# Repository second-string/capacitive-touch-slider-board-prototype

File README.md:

# capacitive-touch-slider-board-prototype

This repo contains a design for a prototype PCB for testing different capacitive touch slider designs. For more information on the different slider footprints, see [writeup](https://brian.team/engineering/capacitive-touch-protoype-pcbs/).

There is a schematic PDF and PCB layer prints PDF in the version 1.0 directory if you do not have KiCad. There are also Excel and interactive BOMs in the `bom/` subdirectory.

Reach out if you would like the KiCad slider schematic symbol and footprint files, they are saved in my global library and so not directly accessible from the project directory.

There is test firmware in `slider-board_rev_1_0/bringup_firmware/`. **NOTE:** This firmware is sloppy, terribly written, inefficient, and everything is hardcoded. It is only included as a reference, do not think that this will work for you out of the box.

Videos of example behavior are in the `img/` directory.

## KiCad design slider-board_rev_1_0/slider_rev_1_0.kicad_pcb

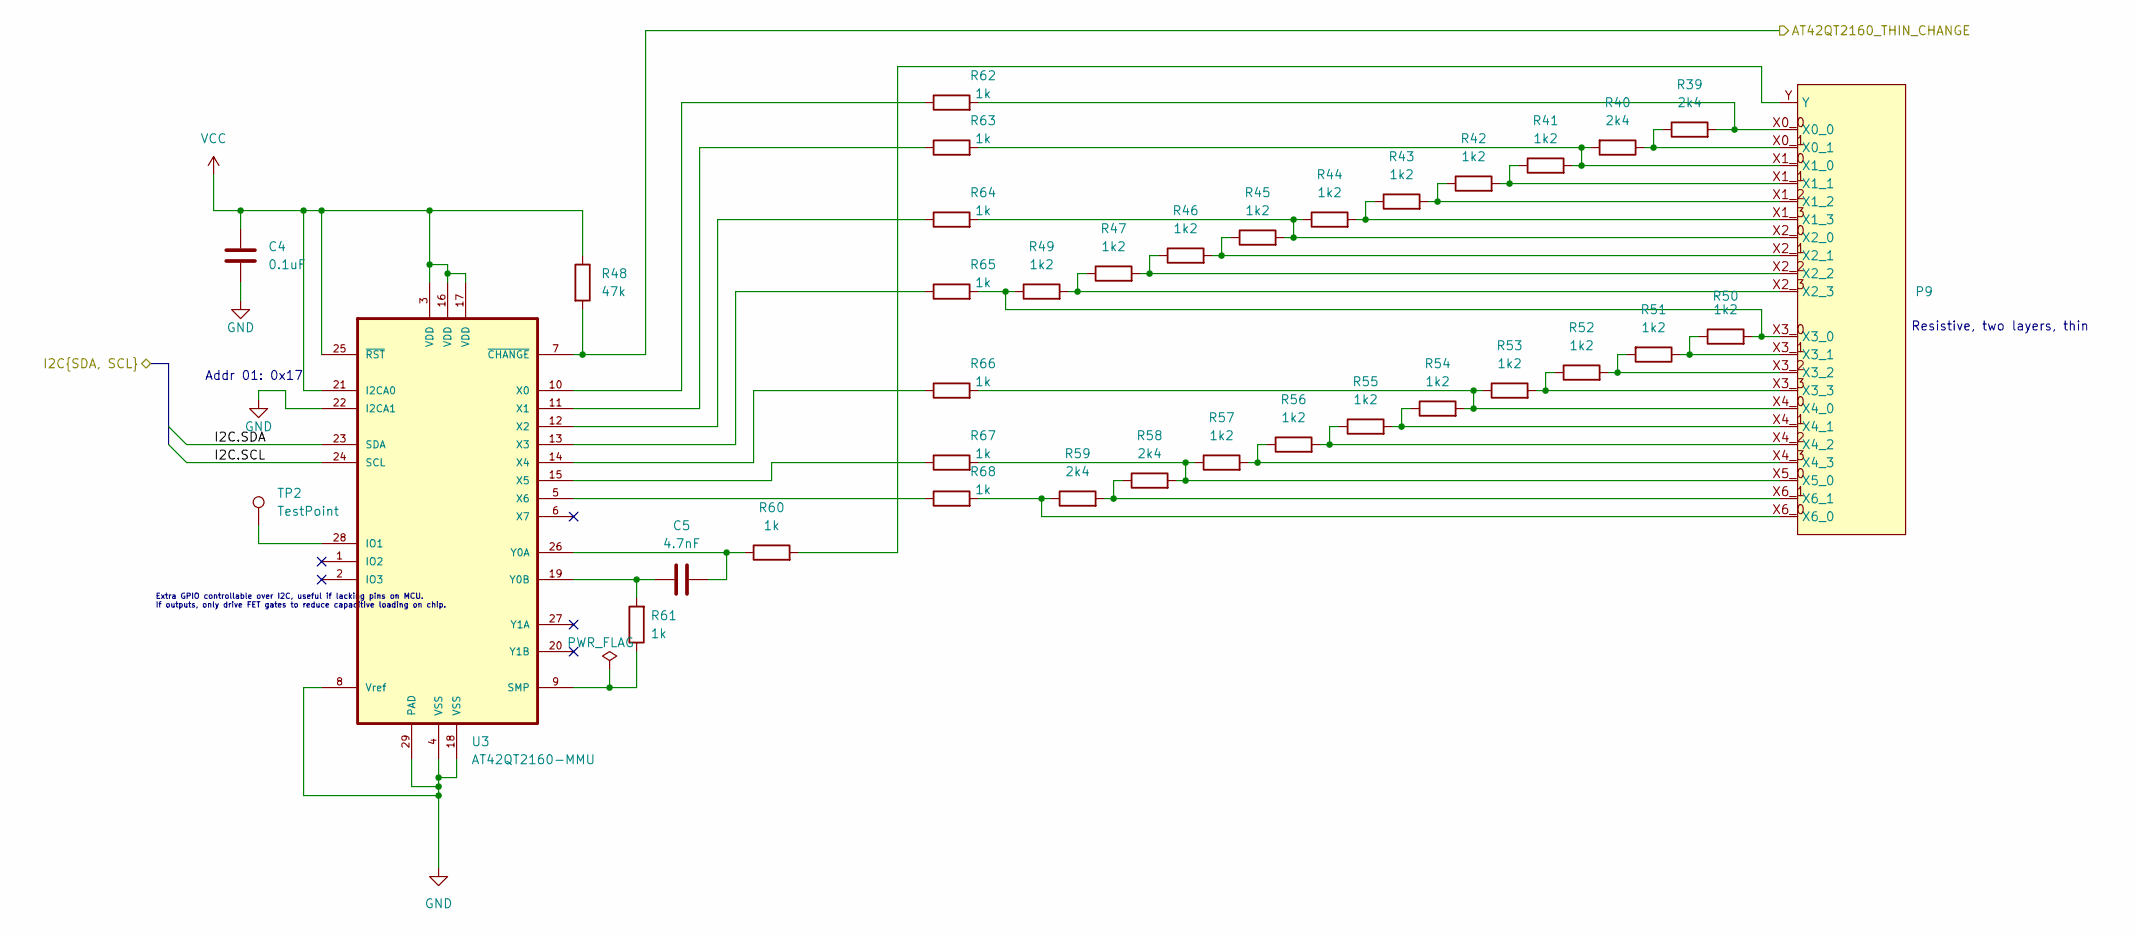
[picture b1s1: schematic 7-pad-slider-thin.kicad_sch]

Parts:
C4: 0.1uF; C_0603_1608Metric
C5: 4.7nF; C_0603_1608Metric
P9: Slider_ResistiveInterpolation_Thin_7P_2L
R39, R40, R58, R59: 2k4; R_0603_1608Metric
R41, R42, R43, R44, R45, R46, R47, R49, R50, R51, R52, R53, R54, R55, R56, R57: 1k2; R_0603_1608Metric
R48: 47k; R_0603_1608Metric
R60, R61, R62, R63, R64, R65, R66, R67, R68: 1k; R_0603_1608Metric
TP2: TestPoint; TestPoint_Pad_D3.0mm
U3: AT42QT2160-MMU; VQFN-28-1EP_4x4mm_P0.45mm_EP2.4x2.4mm_ThermalVias; MPN AT42QT2160-MMU

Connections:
/3-pad-sliders/I2C.SCL: U3.24 (SCL); also elsewhere on the board
/3-pad-sliders/I2C.SDA: U3.23 (SDA); also elsewhere on the board
/7-pad-slider-thin/AT42QT2160_THIN_CHANGE: R48.2, U3.7 (~CHANGE); also elsewhere on the board
GND: C4.2, U3.4 (VSS), U3.8 (Vref), U3.18 (VSS), U3.22 (I2CA1), U3.29 (PAD); also elsewhere on the board
unnamed: P9.X0_0, R39.2, R62.2
unnamed: P9.X0_1, R39.1, R40.1
unnamed: P9.X1_0, R40.2, R41.2, R63.2
unnamed: P9.X1_1, R41.1, R42.2
unnamed: P9.X1_2, R42.1, R43.2
unnamed: P9.X1_3, R43.1, R44.2
unnamed: P9.X2_0, R44.1, R45.2, R64.2
unnamed: P9.X2_1, R45.1, R46.2
unnamed: P9.X2_2, R46.1, R47.2
unnamed: P9.X2_3, R47.1, R49.2
unnamed: P9.X3_0, R49.1, R50.2, R65.2
unnamed: P9.X3_1, R50.1, R51.1
unnamed: P9.X3_2, R51.2, R52.2
unnamed: P9.X3_3, R52.1, R53.2
unnamed: P9.X4_0, R53.1, R54.2, R66.2
unnamed: P9.X4_1, R54.1, R55.2
unnamed: P9.X4_2, R55.1, R56.2
unnamed: P9.X4_3, R56.1, R57.2
unnamed: P9.X5_0, R57.1, R58.2, R67.2
unnamed: P9.X6_0, R59.1, R68.2
unnamed: P9.X6_1, R58.1, R59.2
unnamed: P9.Y, R60.2
unnamed: TP2.1, U3.28 (IO1)
unnamed: R61.1, U3.9 (SMP)
unnamed: R62.1, U3.10 (X0)
unnamed: R63.1, U3.11 (X1)
unnamed: R64.1, U3.12 (X2)
unnamed: R65.1, U3.13 (X3)
unnamed: R66.1, U3.14 (X4)
unnamed: R67.1, U3.15 (X5)
unnamed: R68.1, U3.5 (X6)
unnamed: C5.2, R60.1, U3.26 (Y0A)
unnamed: C5.1, R61.2, U3.19 (Y0B)
VCC: C4.1, R48.1, U3.3 (VDD), U3.16 (VDD), U3.17 (VDD), U3.21 (I2CA0), U3.25 (~RST); also elsewhere on the board

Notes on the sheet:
Resistive, two layers, thin
Extra GPIO controllable over I2C, useful if lacking pins on MCU. If outputs, only drive FET gates to reduce capacitive loading on chip.
Addr 01: 0x17

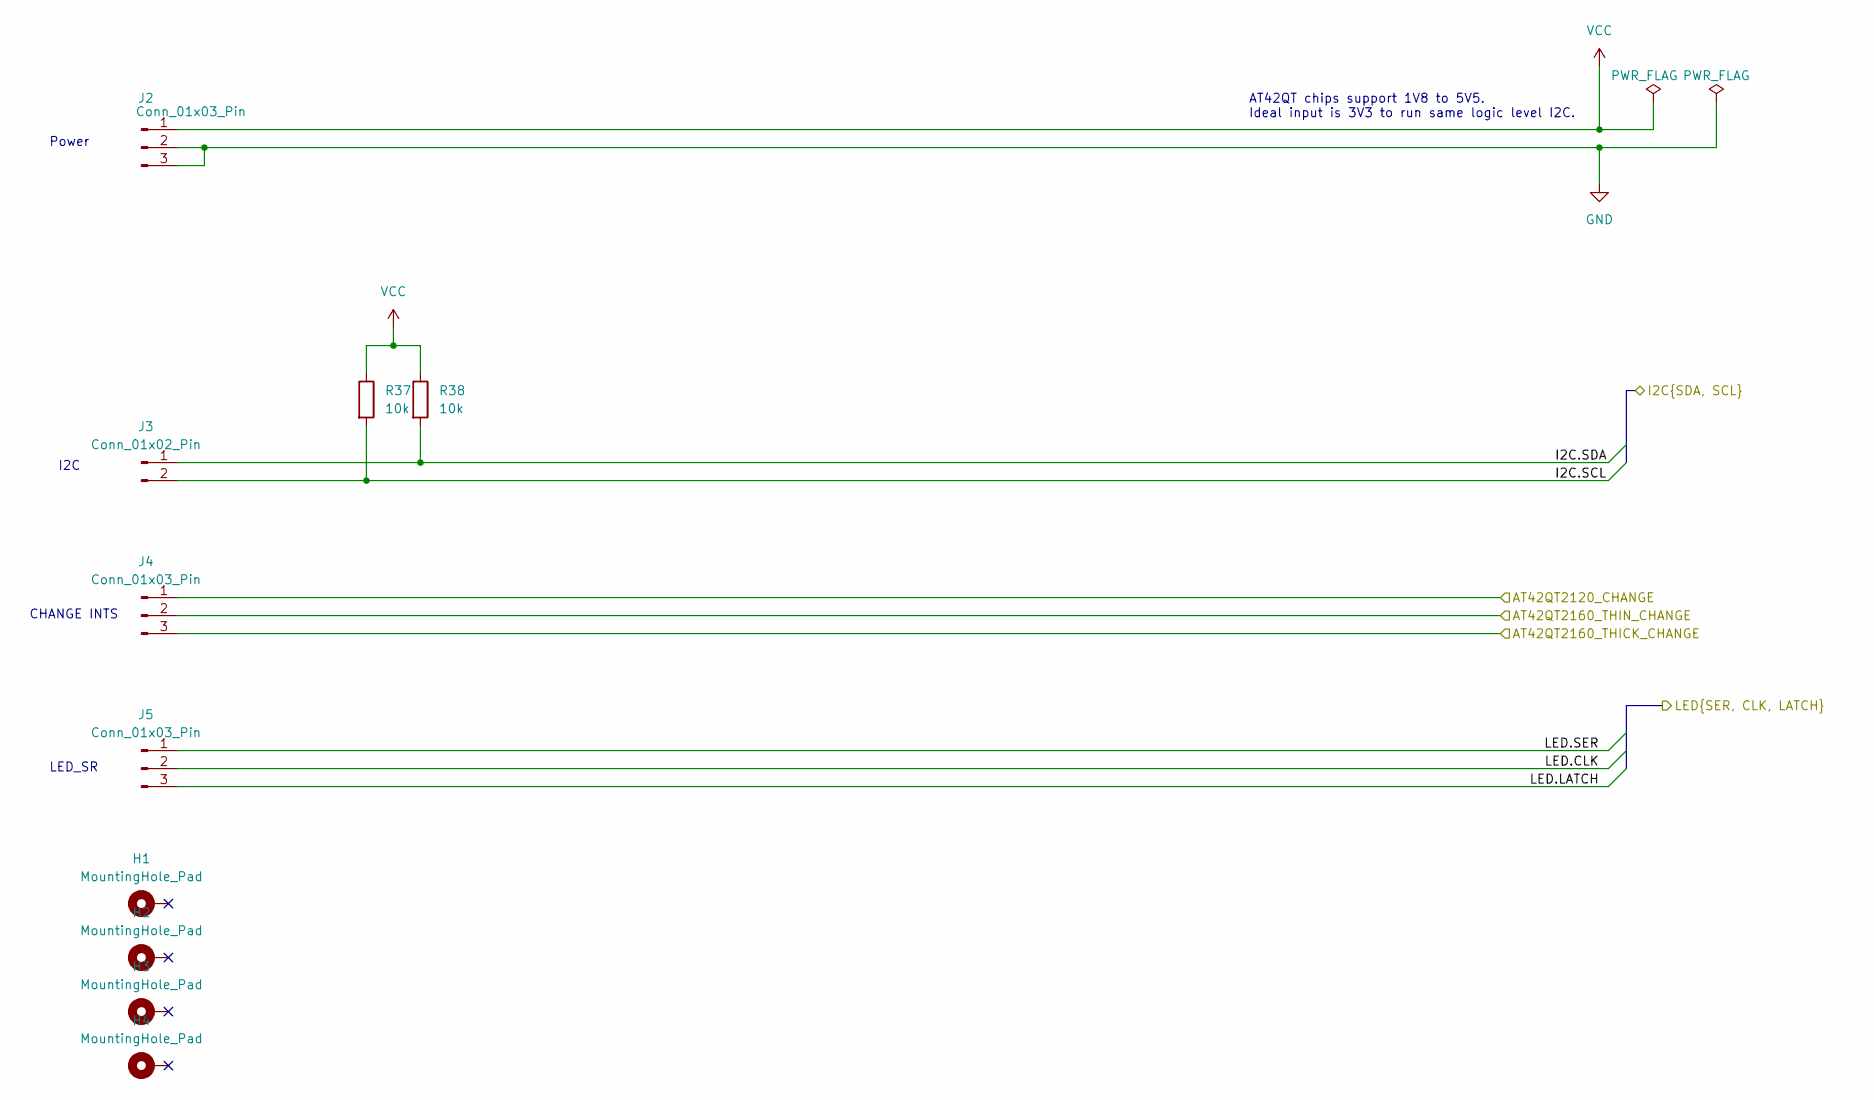
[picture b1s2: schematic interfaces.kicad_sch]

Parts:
H1, H2, H3, H4: MountingHole_Pad; MountingHole_3.2mm_M3_DIN965_Pad
J2, J4, J5: Conn_01x03_Pin; PinHeader_1x03_P2.54mm_Vertical
J3: Conn_01x02_Pin; PinHeader_1x02_P2.54mm_Vertical
R37, R38: 10k; R_0603_1608Metric

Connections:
/3-pad-sliders/AT42QT2120_CHANGE: J4.1; also elsewhere on the board
/3-pad-sliders/I2C.SCL: J3.2, R37.2; also elsewhere on the board
/3-pad-sliders/I2C.SDA: J3.1, R38.2; also elsewhere on the board
/7-pad-slider-thick/AT42QT2160_THICK_CHANGE: J4.3; also elsewhere on the board
/7-pad-slider-thin/AT42QT2160_THIN_CHANGE: J4.2; also elsewhere on the board
/interfaces/LED.CLK: J5.2; also elsewhere on the board
/interfaces/LED.LATCH: J5.3; also elsewhere on the board
/interfaces/LED.SER: J5.1; also elsewhere on the board
GND: J2.2, J2.3; also elsewhere on the board
VCC: J2.1, R37.1, R38.1; also elsewhere on the board

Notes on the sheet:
LED_SR
CHANGE INTS
AT42QT chips support 1V8 to 5V5. Ideal input is 3V3 to run same logic level I2C.
Power
I2C

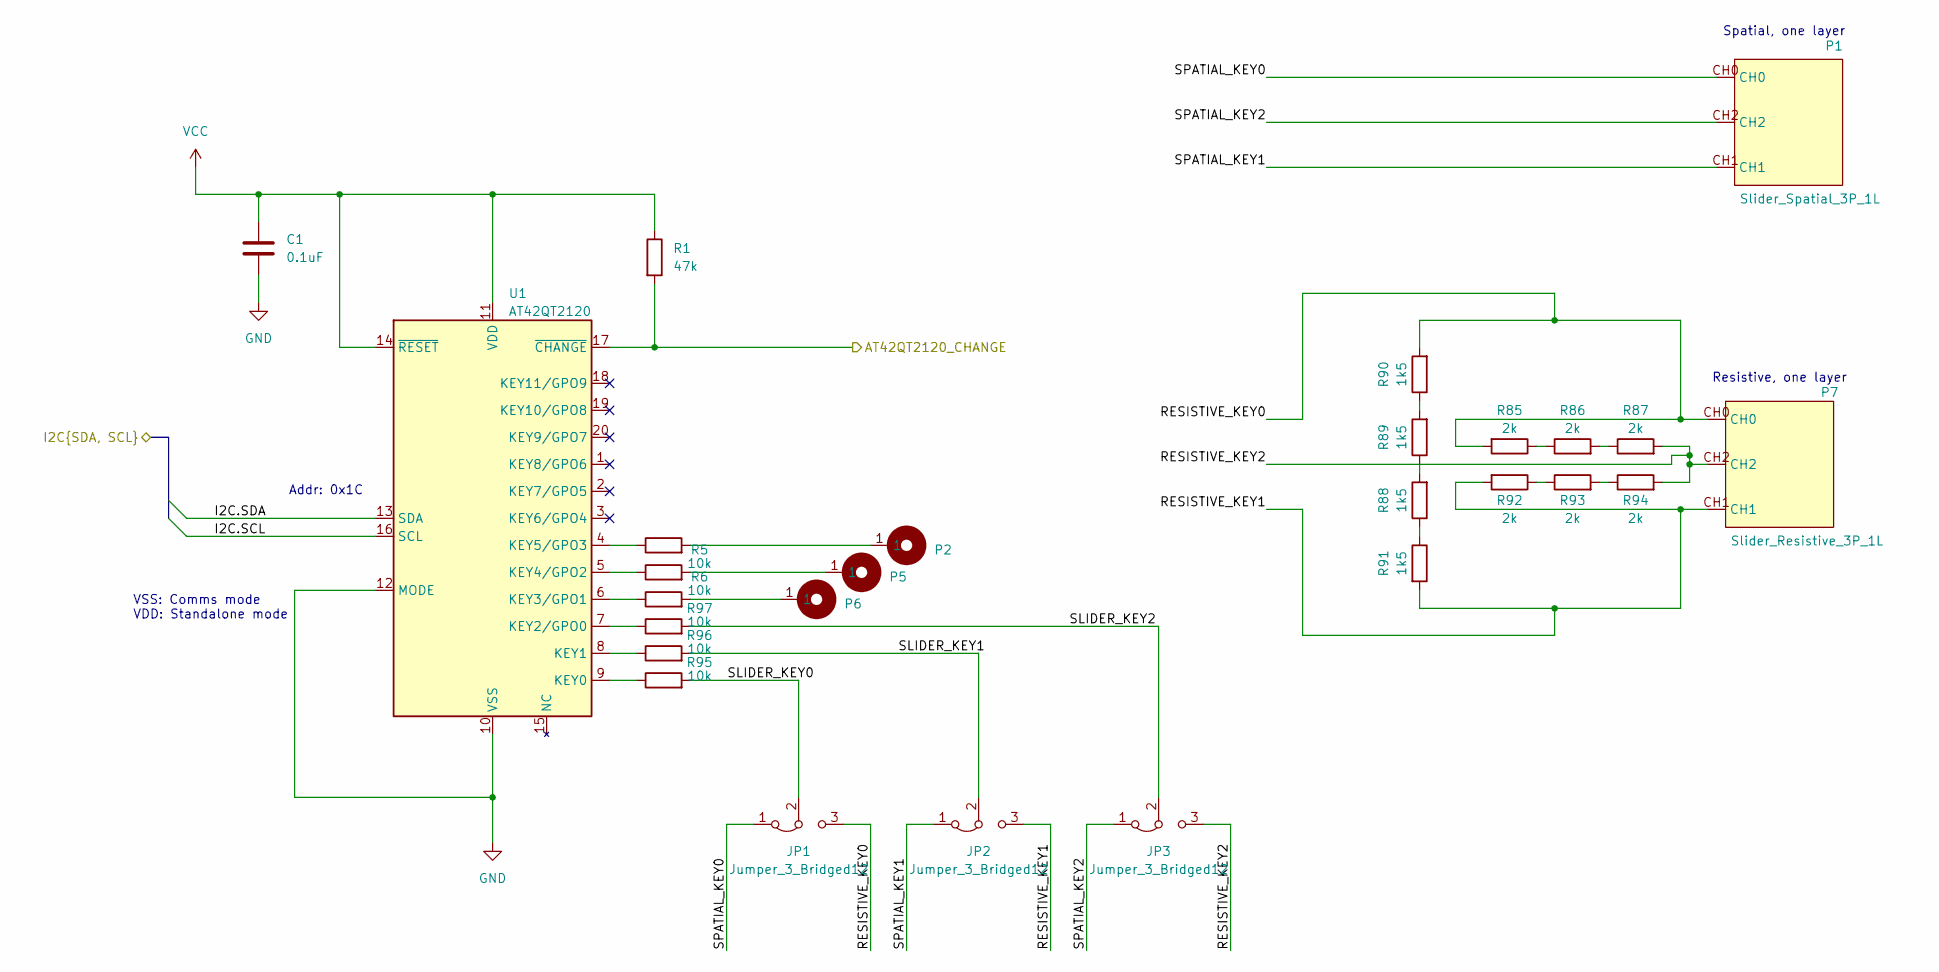
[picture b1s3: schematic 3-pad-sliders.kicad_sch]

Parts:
C1: 0.1uF; C_0603_1608Metric
JP1, JP2, JP3: Jumper_3_Bridged12; PinHeader_1x03_P2.54mm_Vertical
P1: Slider_Spatial_3P_1L; Slider_SpatialInterpolation_3P_1L
P2, P5, P6: Cap_Touch_Ring_Small
P7: Slider_Resistive_3P_1L; Slider_ResistiveInterpolation_3P_1L
R1: 47k; R_0603_1608Metric
R4, R5, R6, R95, R96, R97: 10k; R_0603_1608Metric
R85, R86, R87, R92, R93, R94: 2k; R_0603_1608Metric
R88, R89, R90, R91: 1k5; R_0603_1608Metric
U1: AT42QT2120; TSSOP-20_4.4x6.5mm_P0.65mm; MPN AT42QT2120-XUR

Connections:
/3-pad-sliders/AT42QT2120_CHANGE: R1.2, U1.17 (~CHANGE); also elsewhere on the board
/3-pad-sliders/I2C.SCL: U1.16 (SCL); also elsewhere on the board
/3-pad-sliders/I2C.SDA: U1.13 (SDA); also elsewhere on the board
/3-pad-sliders/RESISTIVE_KEY0: JP1.3 (B), P7.CH0, R85.2, R90.2
/3-pad-sliders/RESISTIVE_KEY1: JP2.3 (B), P7.CH1, R91.2, R92.2
/3-pad-sliders/RESISTIVE_KEY2: JP3.3 (B), P7.CH2, R87.2, R94.2
/3-pad-sliders/SLIDER_KEY0: JP1.2 (C), R95.2
/3-pad-sliders/SLIDER_KEY1: JP2.2 (C), R96.2
/3-pad-sliders/SLIDER_KEY2: JP3.2 (C), R97.2
/3-pad-sliders/SPATIAL_KEY0: JP1.1 (A), P1.CH0
/3-pad-sliders/SPATIAL_KEY1: JP2.1 (A), P1.CH1
/3-pad-sliders/SPATIAL_KEY2: JP3.1 (A), P1.CH2
GND: C1.2, U1.10 (VSS), U1.12 (MODE); also elsewhere on the board
unnamed: P2.1, R4.2
unnamed: P5.1, R5.2
unnamed: P6.1, R6.2
unnamed: R85.1, R86.1
unnamed: R86.2, R87.1
unnamed: R88.1, R91.1
unnamed: R88.2, R89.1
unnamed: R89.2, R90.1
unnamed: R92.1, R93.1
unnamed: R93.2, R94.1
unnamed: R95.1, U1.9 (KEY0)
unnamed: R96.1, U1.8 (KEY1)
unnamed: R97.1, U1.7 (KEY2/GPO0)
unnamed: R6.1, U1.6 (KEY3/GPO1)
unnamed: R5.1, U1.5 (KEY4/GPO2)
unnamed: R4.1, U1.4 (KEY5/GPO3)
VCC: C1.1, R1.1, U1.11 (VDD), U1.14 (~RESET); also elsewhere on the board

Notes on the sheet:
Resistive, one layer
VSS: Comms mode VDD: Standalone mode
Spatial, one layer
Addr: 0x1C

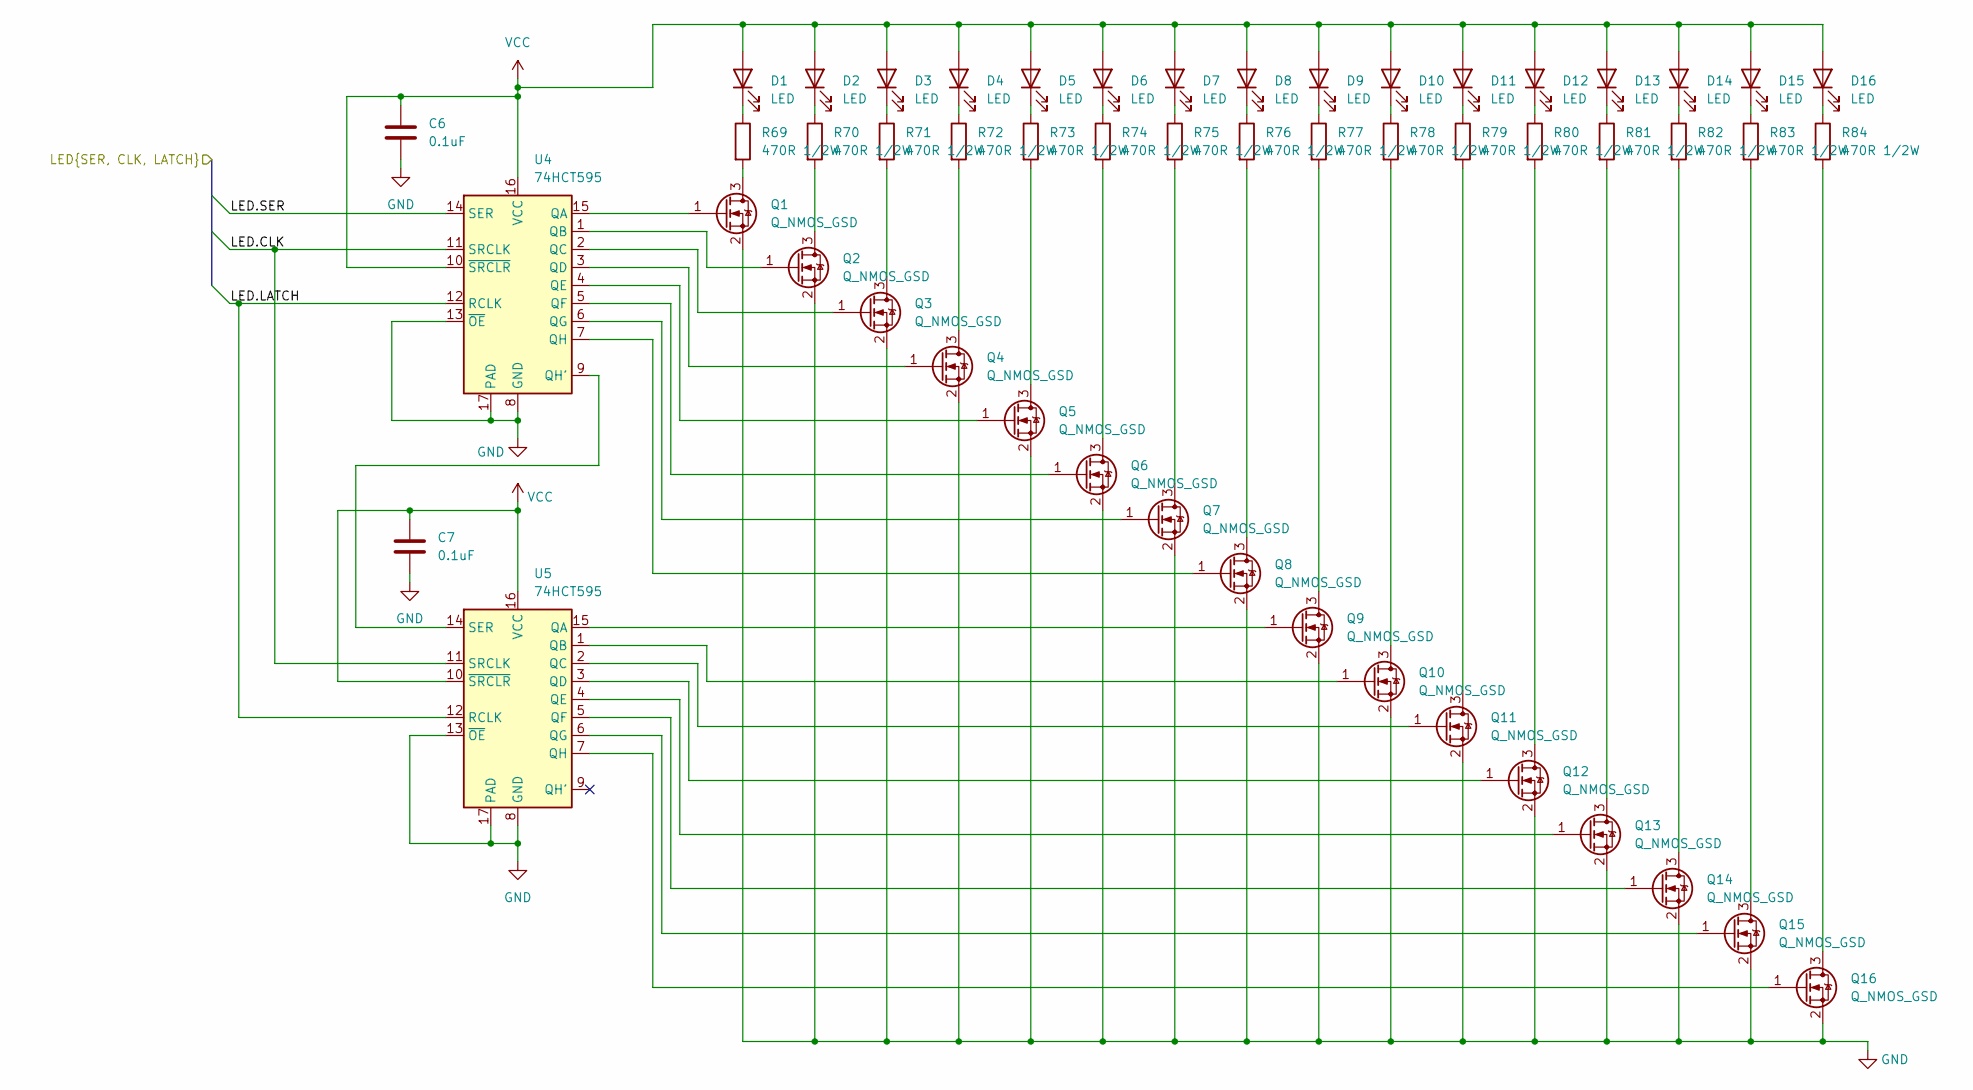
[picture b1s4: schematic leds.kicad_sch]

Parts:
C6, C7: 0.1uF; C_0603_1608Metric
D1, D2, D3, D4, D5, D6, D7, D8, D9, D10, D11, D12, D13, D14, D15, D16: LED; LED_SunLED_XZ_Reverse_Mount
Q1, Q2, Q3, Q4, Q5, Q6, Q7, Q8, Q9, Q10, Q11, Q12, Q13, Q14, Q15, Q16: Q_NMOS_GSD; TSOT-23
R69, R70, R71, R72, R73, R74, R75, R76, R77, R78, R79, R80, R81, R82, R83, R84: 470R 1/2W; R_0603_1608Metric
U4, U5: 74HCT595; DHVQFN-16-1EP_2.5x3.5mm_P0.5mm_EP1x2mm

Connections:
/interfaces/LED.CLK: U4.11 (SRCLK), U5.11 (SRCLK); also elsewhere on the board
/interfaces/LED.LATCH: U4.12 (RCLK), U5.12 (RCLK); also elsewhere on the board
/interfaces/LED.SER: U4.14 (SER); also elsewhere on the board
GND: C6.2, C7.2, Q1.2 (S), Q2.2 (S), Q3.2 (S), Q4.2 (S), Q5.2 (S), Q6.2 (S), Q7.2 (S), Q8.2 (S), Q9.2 (S), Q10.2 (S), Q11.2 (S), Q12.2 (S), Q13.2 (S), Q14.2 (S), Q15.2 (S), Q16.2 (S), U4.8 (GND), U4.13 (~OE), U4.17 (PAD), U5.8 (GND), U5.13 (~OE), U5.17 (PAD); also elsewhere on the board
unnamed: D1.1 (K), R69.1
unnamed: D2.1 (K), R70.1
unnamed: D3.1 (K), R71.1
unnamed: D4.1 (K), R72.1
unnamed: D5.1 (K), R73.1
unnamed: D6.1 (K), R74.1
unnamed: D7.1 (K), R75.1
unnamed: D8.1 (K), R76.1
unnamed: D9.1 (K), R77.1
unnamed: D10.1 (K), R78.1
unnamed: D11.1 (K), R79.1
unnamed: D12.1 (K), R80.1
unnamed: D13.1 (K), R81.1
unnamed: D14.1 (K), R82.1
unnamed: D15.1 (K), R83.1
unnamed: D16.1 (K), R84.1
unnamed: Q1.3 (D), R69.2
unnamed: Q1.1 (G), U4.15 (QA)
unnamed: Q2.3 (D), R70.2
unnamed: Q2.1 (G), U4.1 (QB)
unnamed: Q3.3 (D), R71.2
unnamed: Q3.1 (G), U4.2 (QC)
unnamed: Q4.3 (D), R72.2
unnamed: Q4.1 (G), U4.3 (QD)
unnamed: Q5.3 (D), R73.2
unnamed: Q5.1 (G), U4.4 (QE)
unnamed: Q6.3 (D), R74.2
unnamed: Q6.1 (G), U4.5 (QF)
unnamed: Q7.3 (D), R75.2
unnamed: Q7.1 (G), U4.6 (QG)
unnamed: Q8.3 (D), R76.2
unnamed: Q8.1 (G), U4.7 (QH)
unnamed: Q9.3 (D), R77.2
unnamed: Q9.1 (G), U5.15 (QA)
unnamed: Q10.3 (D), R78.2
unnamed: Q10.1 (G), U5.1 (QB)
unnamed: Q11.3 (D), R79.2
unnamed: Q11.1 (G), U5.2 (QC)
unnamed: Q12.3 (D), R80.2
unnamed: Q12.1 (G), U5.3 (QD)
unnamed: Q13.3 (D), R81.2
unnamed: Q13.1 (G), U5.4 (QE)
unnamed: Q14.3 (D), R82.2
unnamed: Q14.1 (G), U5.5 (QF)
unnamed: Q15.3 (D), R83.2
unnamed: Q15.1 (G), U5.6 (QG)
unnamed: Q16.3 (D), R84.2
unnamed: Q16.1 (G), U5.7 (QH)
unnamed: U4.9 (QH'), U5.14 (SER)
VCC: C6.1, C7.1, D1.2 (A), D2.2 (A), D3.2 (A), D4.2 (A), D5.2 (A), D6.2 (A), D7.2 (A), D8.2 (A), D9.2 (A), D10.2 (A), D11.2 (A), D12.2 (A), D13.2 (A), D14.2 (A), D15.2 (A), D16.2 (A), U4.10 (~SRCLR), U4.16 (VCC), U5.10 (~SRCLR), U5.16 (VCC); also elsewhere on the board

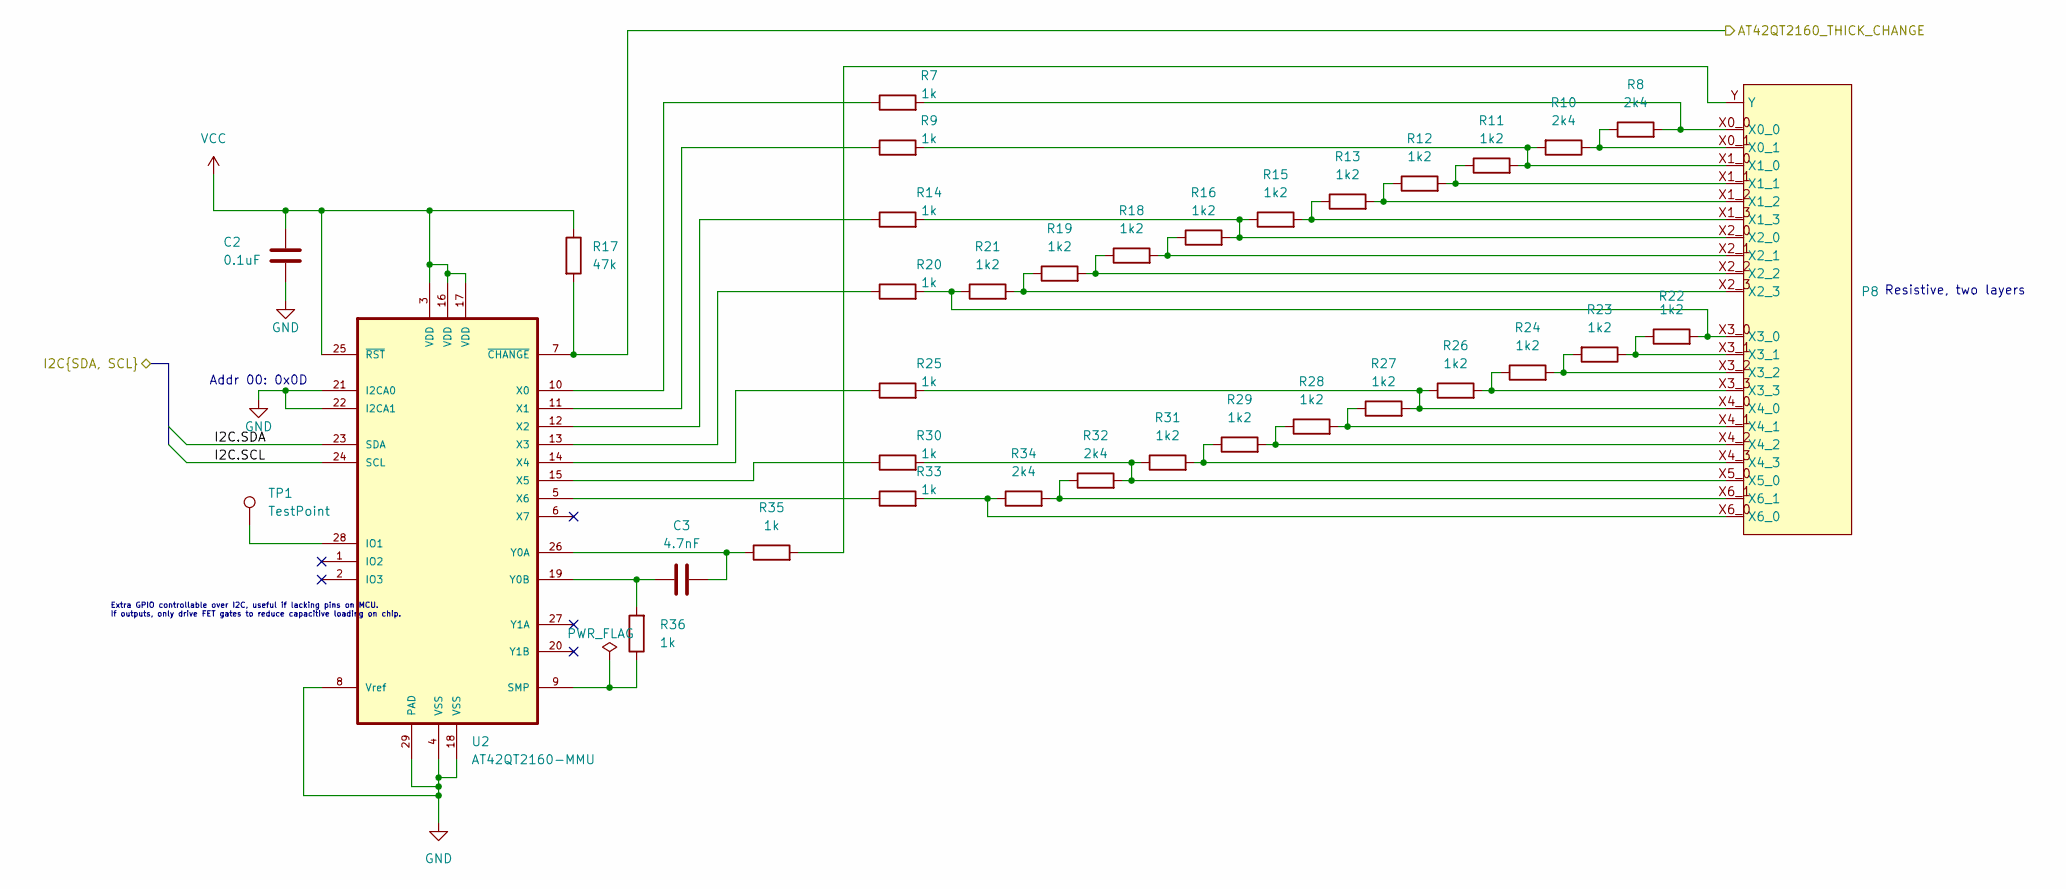
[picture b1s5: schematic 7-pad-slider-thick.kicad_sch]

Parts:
C2: 0.1uF; C_0603_1608Metric
C3: 4.7nF; C_0603_1608Metric
P8: Slider_ResistiveInterpolation_7P_2L
R7, R9, R14, R20, R25, R30, R33, R35, R36: 1k; R_0603_1608Metric
R8, R10, R32, R34: 2k4; R_0603_1608Metric
R11, R12, R13, R15, R16, R18, R19, R21, R22, R23, R24, R26, R27, R28, R29, R31: 1k2; R_0603_1608Metric
R17: 47k; R_0603_1608Metric
TP1: TestPoint; TestPoint_Pad_D3.0mm
U2: AT42QT2160-MMU; VQFN-28-1EP_4x4mm_P0.45mm_EP2.4x2.4mm_ThermalVias; MPN AT42QT2160-MMU

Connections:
/3-pad-sliders/I2C.SCL: U2.24 (SCL); also elsewhere on the board
/3-pad-sliders/I2C.SDA: U2.23 (SDA); also elsewhere on the board
/7-pad-slider-thick/AT42QT2160_THICK_CHANGE: R17.2, U2.7 (~CHANGE); also elsewhere on the board
GND: C2.2, U2.4 (VSS), U2.8 (Vref), U2.18 (VSS), U2.21 (I2CA0), U2.22 (I2CA1), U2.29 (PAD); also elsewhere on the board
unnamed: P8.X0_0, R7.2, R8.2
unnamed: P8.X0_1, R8.1, R10.1
unnamed: P8.X1_0, R9.2, R10.2, R11.2
unnamed: P8.X1_1, R11.1, R12.2
unnamed: P8.X1_2, R12.1, R13.2
unnamed: P8.X1_3, R13.1, R15.2
unnamed: P8.X2_0, R14.2, R15.1, R16.2
unnamed: P8.X2_1, R16.1, R18.2
unnamed: P8.X2_2, R18.1, R19.2
unnamed: P8.X2_3, R19.1, R21.2
unnamed: P8.X3_0, R20.2, R21.1, R22.2
unnamed: P8.X3_1, R22.1, R23.1
unnamed: P8.X3_2, R23.2, R24.2
unnamed: P8.X3_3, R24.1, R26.2
unnamed: P8.X4_0, R25.2, R26.1, R27.2
unnamed: P8.X4_1, R27.1, R28.2
unnamed: P8.X4_2, R28.1, R29.2
unnamed: P8.X4_3, R29.1, R31.2
unnamed: P8.X5_0, R30.2, R31.1, R32.2
unnamed: P8.X6_0, R33.2, R34.1
unnamed: P8.X6_1, R32.1, R34.2
unnamed: P8.Y, R35.2
unnamed: TP1.1, U2.28 (IO1)
unnamed: R36.1, U2.9 (SMP)
unnamed: R7.1, U2.10 (X0)
unnamed: R9.1, U2.11 (X1)
unnamed: R14.1, U2.12 (X2)
unnamed: R20.1, U2.13 (X3)
unnamed: R25.1, U2.14 (X4)
unnamed: R30.1, U2.15 (X5)
unnamed: R33.1, U2.5 (X6)
unnamed: C3.2, R35.1, U2.26 (Y0A)
unnamed: C3.1, R36.2, U2.19 (Y0B)
VCC: C2.1, R17.1, U2.3 (VDD), U2.16 (VDD), U2.17 (VDD), U2.25 (~RST); also elsewhere on the board

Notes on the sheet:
Addr 00: 0x0D
Extra GPIO controllable over I2C, useful if lacking pins on MCU. If outputs, only drive FET gates to reduce capacitive loading on chip.
Resistive, two layers

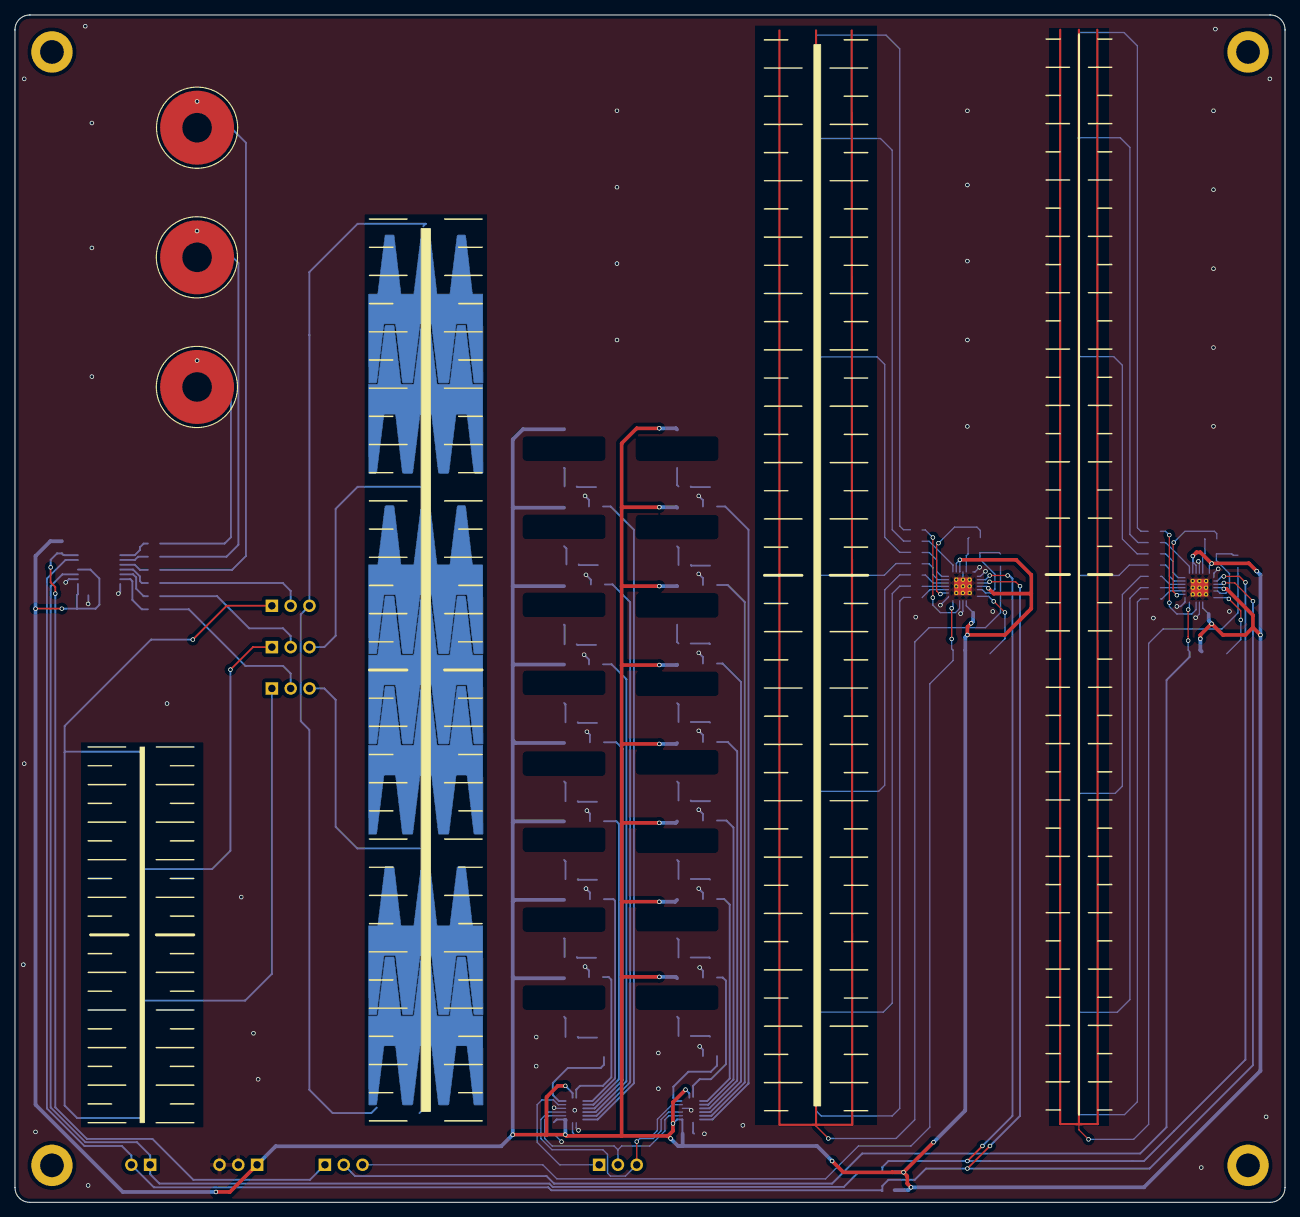
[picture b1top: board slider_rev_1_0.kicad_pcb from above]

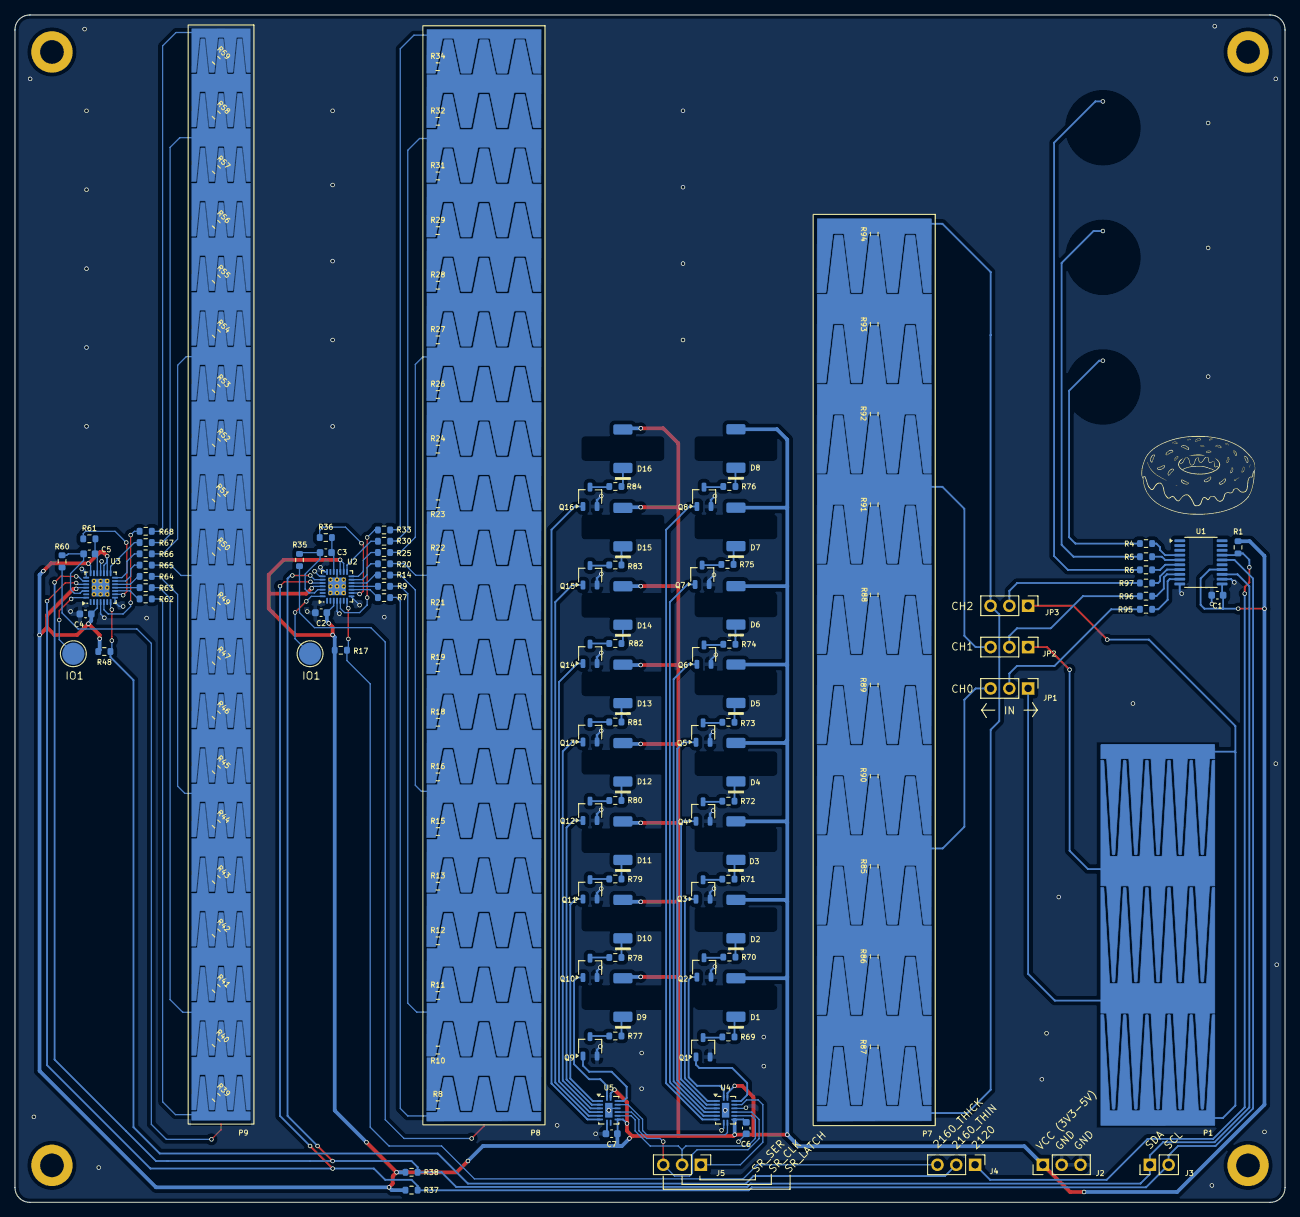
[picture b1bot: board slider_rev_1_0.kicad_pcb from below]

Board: 2 copper layers, 171.7 x 160.5 mm, 159 parts (152 on the bottom side), 150 nets.

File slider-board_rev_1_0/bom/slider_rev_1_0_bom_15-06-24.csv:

"Reference","Value","Footprint","Qty","DNP","Digikey","MPN","Purchase-URL"
"C1,C2,C4,C6,C7","0.1uF","Capacitor_SMD:C_0603_1608Metric","5","","","",""
"C3,C5","4.7nF","Capacitor_SMD:C_0603_1608Metric","2","","","",""
"D1,D2,D3,D4,D5,D6,D7,D8,D9,D10,D11,D12,D13,D14,D15,D16","LED","LED_SMD:LED_SunLED_XZ_Reverse_Mount","16","","","",""
"J2,J4,J5","Conn_01x03_Pin","Connector_PinHeader_2.54mm:PinHeader_1x03_P2.54mm_Vertical","3","","","",""
"J3","Conn_01x02_Pin","Connector_PinHeader_2.54mm:PinHeader_1x02_P2.54mm_Vertical","1","","","",""
"P1","Slider_Spatial_3P_1L","Touch:Slider_SpatialInterpolation_3P_1L","1","","","",""
"P2,P5,P6,P8,P9","~","-- mixed values --","5","","","",""
"P7","Slider_Resistive_3P_1L","Touch:Slider_ResistiveInterpolation_3P_1L","1","","","",""
"Q1,Q2,Q3,Q4,Q5,Q6,Q7,Q8,Q9,Q10,Q11,Q12,Q13,Q14,Q15,Q16","Q_NMOS_GSD","Package_TO_SOT_SMD:TSOT-23","16","","","",""
"R1,R17,R48","47k","Resistor_SMD:R_0603_1608Metric","3","","","",""
"R4,R5,R6,R37,R38,R95,R96,R97","10k","Resistor_SMD:R_0603_1608Metric","8","","","",""
"R7,R9,R14,R20,R25,R30,R33,R35,R36,R60,R61,R62,R63,R64,R65,R66,R67,R68","1k","Resistor_SMD:R_0603_1608Metric","18","","","",""
"R8,R10,R32,R34,R39,R40,R58,R59","2k4","Resistor_SMD:R_0603_1608Metric","8","","","",""
"R11,R12,R13,R15,R16,R18,R19,R21,R22,R23,R24,R26,R27,R28,R29,R31,R41,R42,R43,R44,R45,R46,R47,R49,R50,R51,R52,R53,R54,R55,R56,R57","1k2","Resistor_SMD:R_0603_1608Metric","32","","","",""
"R69,R70,R71,R72,R73,R74,R75,R76,R77,R78,R79,R80,R81,R82,R83,R84","470R 1/2W","Resistor_SMD:R_0603_1608Metric","16","","","",""
"R85,R86,R87,R92,R93,R94","2k","Resistor_SMD:R_0603_1608Metric","6","","","",""
"R88,R89,R90,R91","1k5","Resistor_SMD:R_0603_1608Metric","4","","","",""
"TP1,TP2","TestPoint","TestPoint:TestPoint_Pad_D3.0mm","2","","","",""
"U1","AT42QT2120","Package_SO:TSSOP-20_4.4x6.5mm_P0.65mm","1","","https://www.digikey.de/en/products/detail/microchip-technolo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","AT42QT2120-XUR",""
"U2,U3","AT42QT2160-MMU","Package_DFN_QFN:VQFN-28-1EP_4x4mm_P0.45mm_EP2.4x2.4mm_ThermalVias","2","","","AT42QT2160-MMU","https://www.snapeda.com/api/url_track_click_mouser/?unipart_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"
"U4,U5","74HCT595","Package_DFN_QFN:DHVQFN-16-1EP_2.5x3.5mm_P0.5mm_EP1x2mm","2","","","",""

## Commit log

2024-10-19 Initial commit to host files for reference
